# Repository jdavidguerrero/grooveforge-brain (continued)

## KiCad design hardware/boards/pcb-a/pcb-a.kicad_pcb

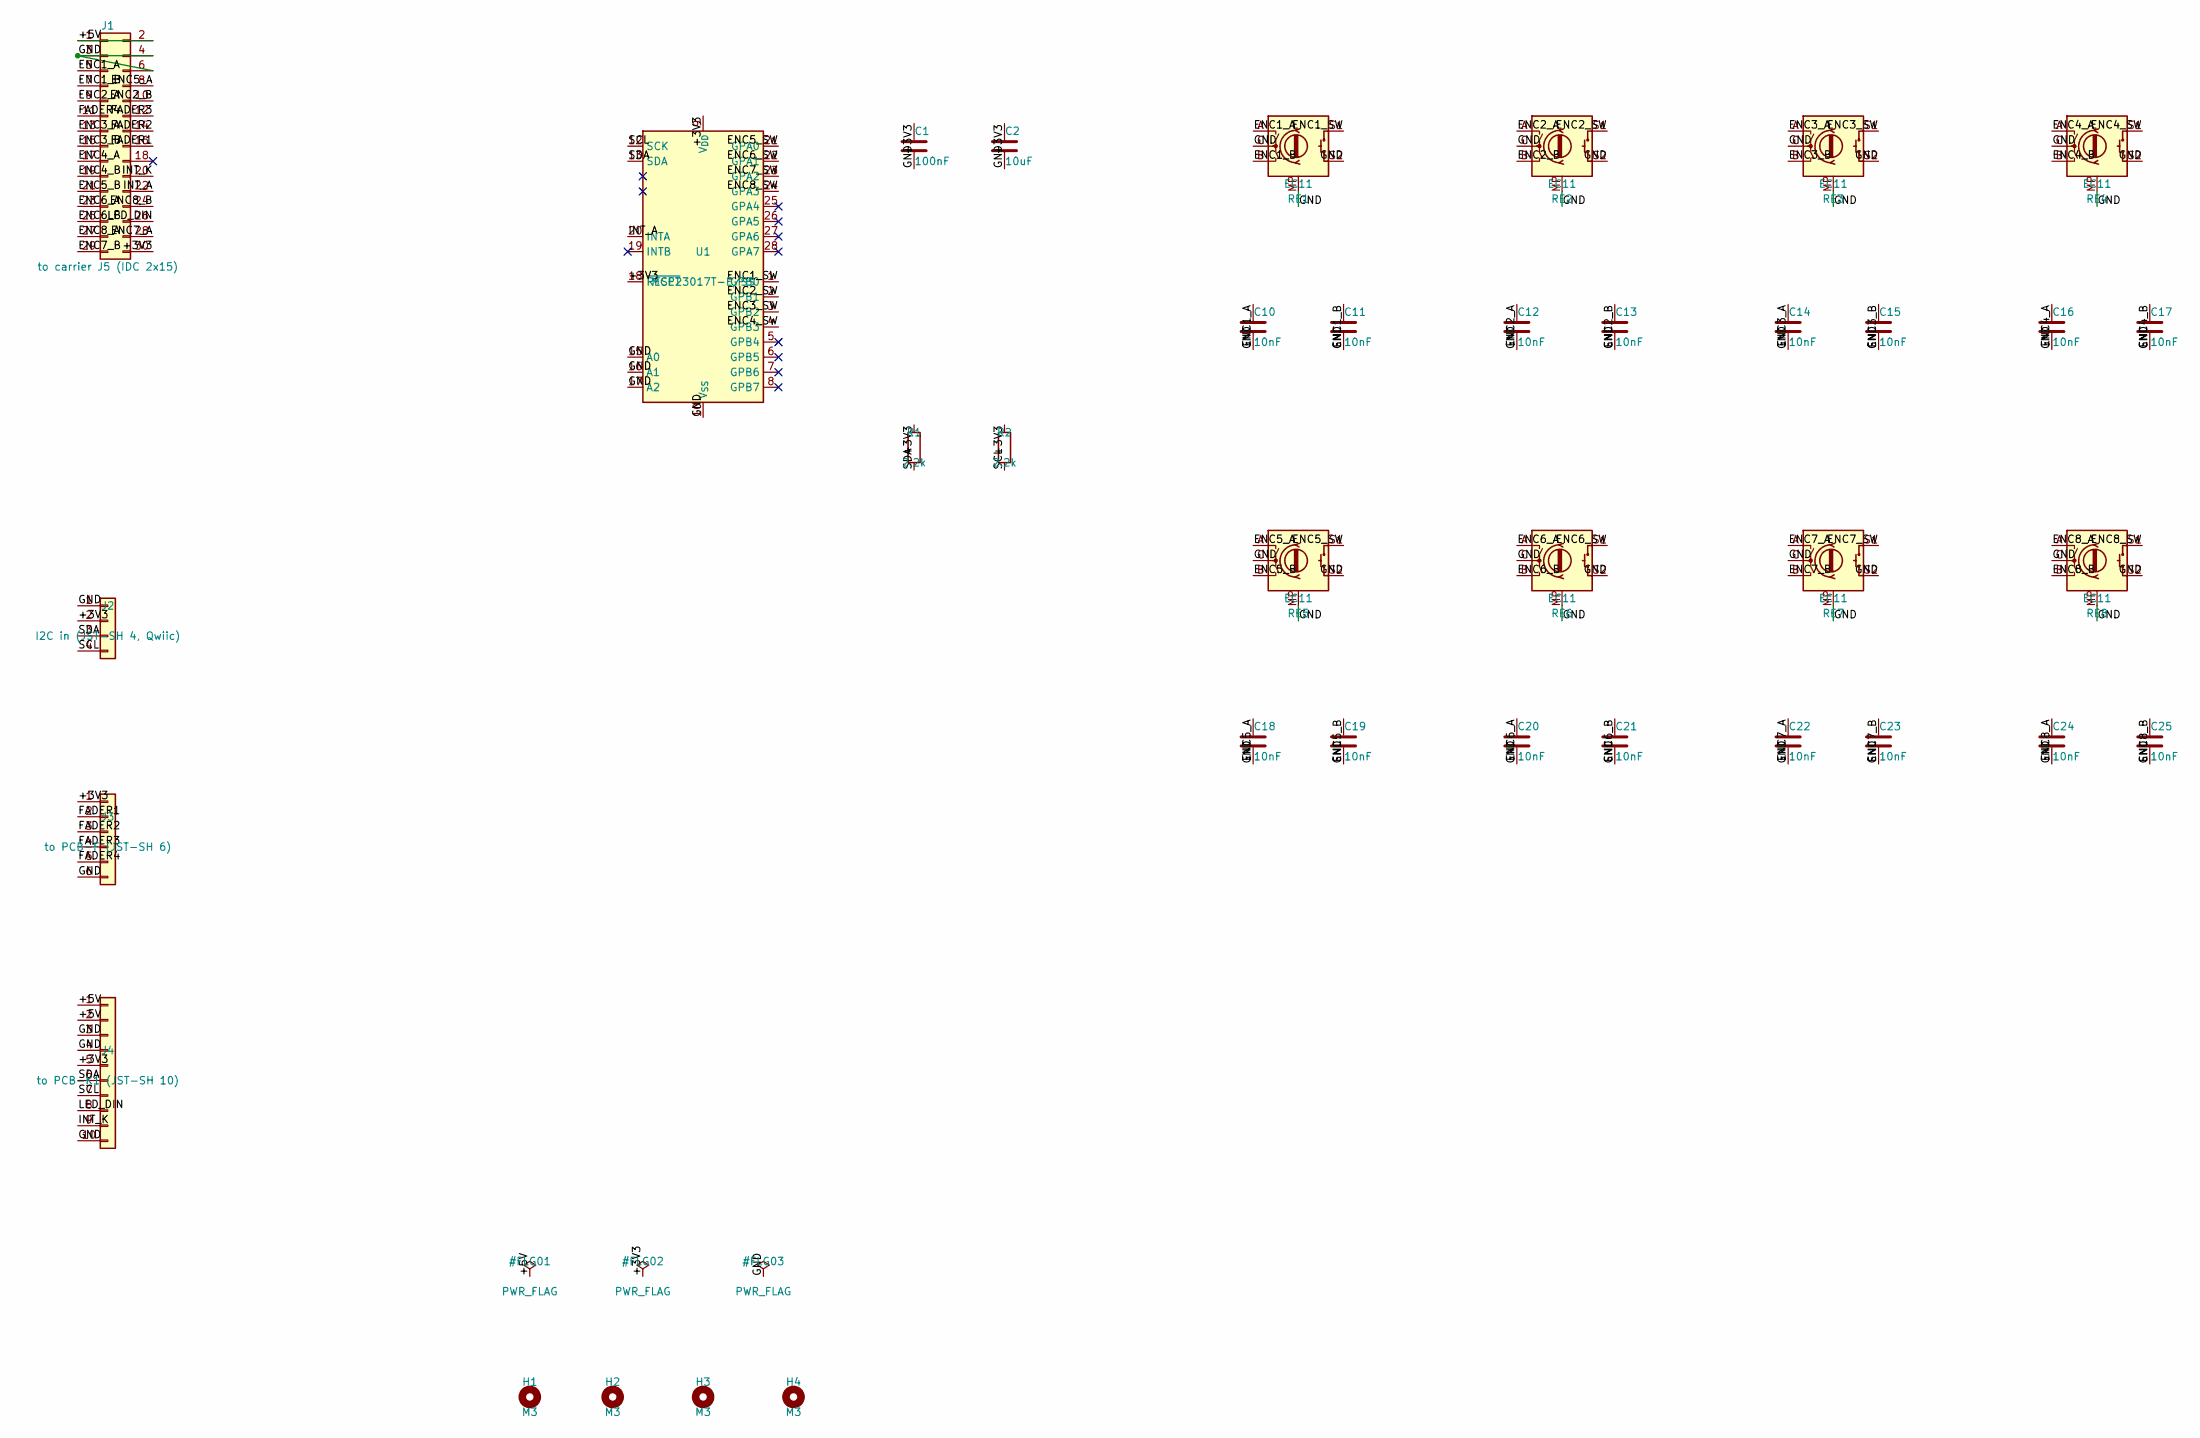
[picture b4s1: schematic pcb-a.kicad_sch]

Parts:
C1: 100nF; C_0603_1608Metric; LCSC C14663
C2: 10uF; C_0805_2012Metric; LCSC C15850
C10, C11, C12, C13, C14, C15, C16, C17, C18, C19, C20, C21, C22, C23, C24, C25: 10nF; C_0603_1608Metric; LCSC C57112
H1, H2, H3, H4: M3; MountingHole_3.2mm_M3
J1: to carrier J5 (IDC 2x15); IDC-Header_2x15_P2.54mm_Vertical
J2: I2C in (JST-SH 4, Qwiic); JST_SH_SM04B-SRSS-TB_1x04-1MP_P1.00mm_Horizontal; LCSC C160404
J3: to PCB-F (JST-SH 6); JST_SH_SM06B-SRSS-TB_1x06-1MP_P1.00mm_Horizontal; LCSC C160405
J4: to PCB-K1 (JST-SH 10); JST_SH_SM10B-SRSS-TB_1x10-1MP_P1.00mm_Horizontal; LCSC C160409
R1, R2: 2.2k; R_0603_1608Metric; LCSC C4190
RE1, RE2, RE3, RE4, RE5, RE6, RE7, RE8: EC11; RotaryEncoder_Alps_EC11E-Switch_Vertical_H20mm
U1: MCP23017T-E/SS; SSOP-28_5.3x10.2mm_P0.65mm; LCSC C558584

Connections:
/+3V3: C1.1, C2.1, J1.30, J2.2, J3.1, J4.5, R1.1, R2.1, U1.9 (V_{DD}), U1.18 (~RESET)
/+5V: J1.1, J1.2, J4.1, J4.2
/ENC1_A: C10.1, J1.5, RE1.A
/ENC1_B: C11.1, J1.7, RE1.B
/ENC1_SW: RE1.S1, U1.1 (GPB0)
/ENC2_A: C12.1, J1.9, RE2.A
/ENC2_B: C13.1, J1.10, RE2.B
/ENC2_SW: RE2.S1, U1.2 (GPB1)
/ENC3_A: C14.1, J1.13, RE3.A
/ENC3_B: C15.1, J1.15, RE3.B
/ENC3_SW: RE3.S1, U1.3 (GPB2)
/ENC4_A: C16.1, J1.17, RE4.A
/ENC4_B: C17.1, J1.19, RE4.B
/ENC4_SW: RE4.S1, U1.4 (GPB3)
/ENC5_A: C18.1, J1.8, RE5.A
/ENC5_B: C19.1, J1.21, RE5.B
/ENC5_SW: RE5.S1, U1.21 (GPA0)
/ENC6_A: C20.1, J1.23, RE6.A
/ENC6_B: C21.1, J1.25, RE6.B
/ENC6_SW: RE6.S1, U1.22 (GPA1)
/ENC7_A: C22.1, J1.28, RE7.A
/ENC7_B: C23.1, J1.29, RE7.B
/ENC7_SW: RE7.S1, U1.23 (GPA2)
/ENC8_A: C24.1, J1.27, RE8.A
/ENC8_B: C25.1, J1.24, RE8.B
/ENC8_SW: RE8.S1, U1.24 (GPA3)
/FADER1: J1.16, J3.2
/FADER2: J1.14, J3.3
/FADER3: J1.12, J3.4
/FADER4: J1.11, J3.5
/GND: C1.2, C2.2, C10.2, C11.2, C12.2, C13.2, C14.2, C15.2, C16.2, C17.2, C18.2, C19.2, C20.2, C21.2, C22.2, C23.2, C24.2, C25.2, J1.3, J1.4, J1.6, J2.1, J3.6, J4.3, J4.4, J4.10, RE1.C, RE1.MP, RE1.S2, RE2.C, RE2.MP, RE2.S2, RE3.C, RE3.MP, RE3.S2, RE4.C, RE4.MP, RE4.S2, RE5.C, RE5.MP, RE5.S2, RE6.C, RE6.MP, RE6.S2, RE7.C, RE7.MP, RE7.S2, RE8.C, RE8.MP, RE8.S2, U1.10 (V_{SS}), U1.15 (A0), U1.16 (A1), U1.17 (A2)
/INT_A: J1.22, U1.20 (INTA)
/INT_K: J1.20, J4.9
/LED_DIN: J1.26, J4.8
/SCL: J2.4, J4.7, R2.2, U1.12 (SCK)
/SDA: J2.3, J4.6, R1.2, U1.13 (SDA)

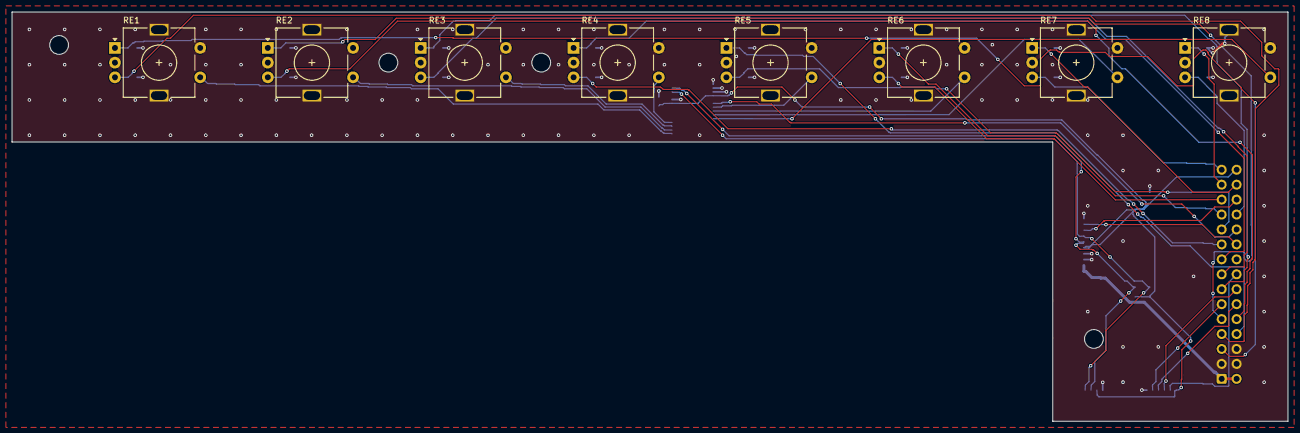
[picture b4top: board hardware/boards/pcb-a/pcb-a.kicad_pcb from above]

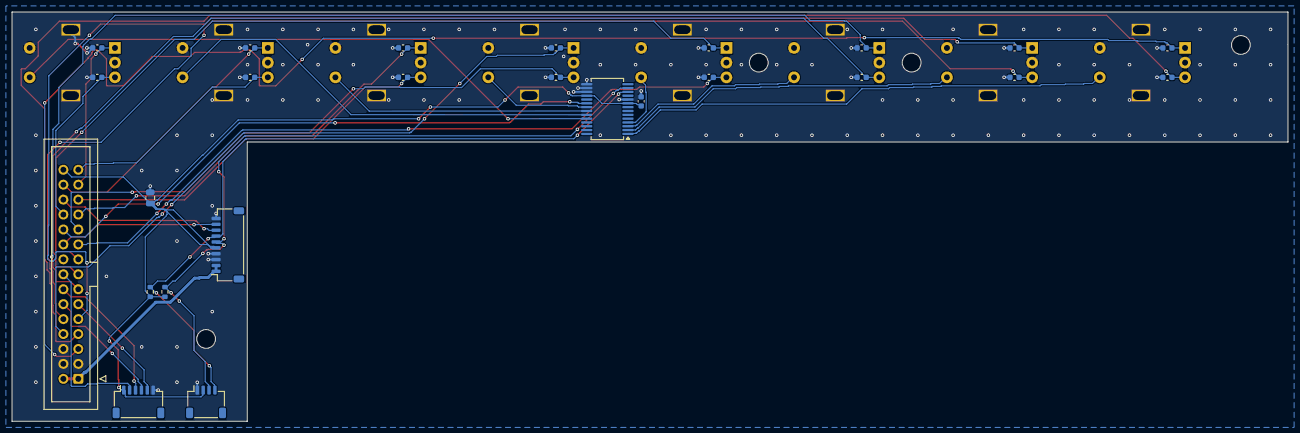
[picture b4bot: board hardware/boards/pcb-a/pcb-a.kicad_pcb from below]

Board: 2 copper layers, 217.0 x 69.6 mm, 37 parts (25 on the bottom side), 36 nets.

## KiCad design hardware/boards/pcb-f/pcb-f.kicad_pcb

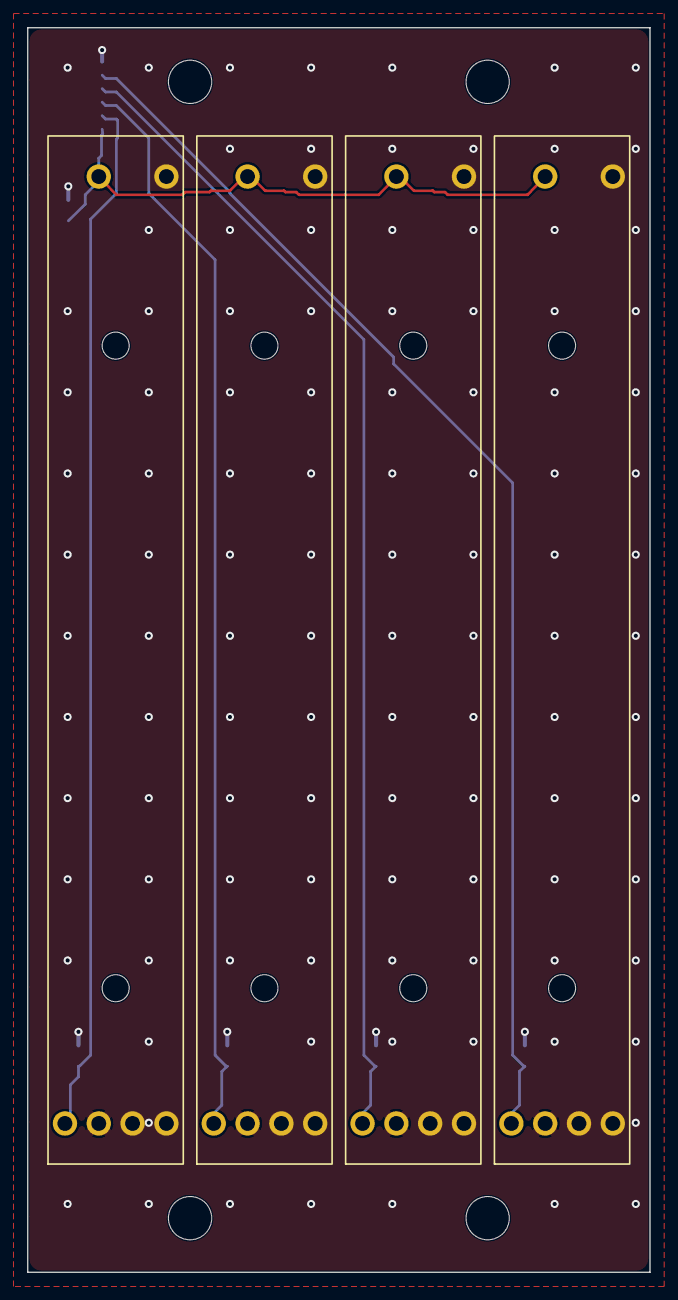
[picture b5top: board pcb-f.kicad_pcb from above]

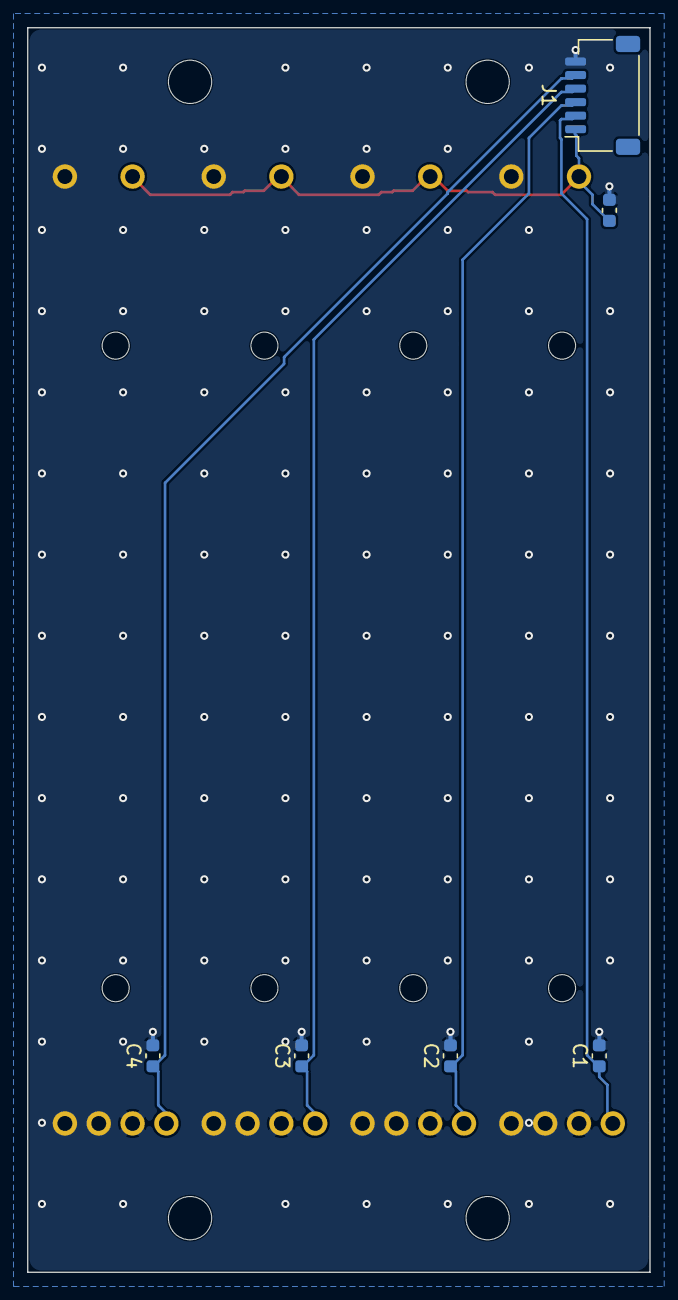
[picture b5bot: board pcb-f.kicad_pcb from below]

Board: 2 copper layers, 46.0 x 92.0 mm, 14 parts (6 on the bottom side), 6 nets.

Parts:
C1, C2, C3, C4, C5: 100nF; C_0603_1608Metric
H1, H2, H3, H4: M3; MountingHole_3.2mm_M3
J1: to PCB-A (JST-SH 6); JST_SH_SM06B-SRSS-TB_1x06-1MP_P1.00mm_Horizontal
RV1, RV2, RV3, RV4: RS6011 B50K; ALPS_RS6011P_60mm

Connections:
/+3V3: C5.1, J1.1, RV1.3, RV2.3, RV3.3, RV4.3
/FADER1: C1.1, J1.2, RV1.2
/FADER2: C2.1, J1.3, RV2.2
/FADER3: C3.1, J1.4, RV3.2
/FADER4: C4.1, J1.5, RV4.2
/GND: C1.2, C2.2, C3.2, C4.2, C5.2, J1.6, RV1.1, RV1.MP, RV2.1, RV2.MP, RV3.1, RV3.MP, RV4.1, RV4.MP
